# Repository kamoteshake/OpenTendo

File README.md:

<br />

# Open 'Tendo
An Open-Source HardWare (OSHW) recreation of the original 1985 Front-Loading NES motherboard.

## Note on RGB and HDMI

Neither RGB nor HDMI video output were or are a goal of the OpenTendo project, the goal was/is documentation and preservation, and the project was an exercise in reverse engineering. As such "improved" video outputs will not be added to OpenTendo.

NESRGB and Hi-Def NES can be installed as normal, but will not be incorporated into the OpenTendo PCB

## Repository Structure
### Branches
| Branch | Description |
| ------ | ----------- |
| master | Latest revision of OpenTendo. This is a almost 1:1 of the OEM NES. |
| modded | Modded version of the latest revision (`master`). This houses any modification that is not in the OEM NES. |
| vX.X | Previous revisions of OpenTendo. (*ex.* v1.3) |
| vX.X_modded | Modded version of a previous revision. (*ex.* v1.3_modded) |

### File Structure
```
.
├── BOM              # Contains the bill of materials.
├── Board Files      # Contains all files necessary to open the project in KiCad.
|   └── Libraries    # Contains a library of all of the custom footprints used on the board.
├── Scans            # Contains the scans of the OEM NES board.
└── Schematics       # Contains schematics for the OEM frontloading NES board revisions,
                       some schematics represent more than one revision
```

The gerber files required to order PCBs can be found under [releases](https://github.com/Redherring32/OpenTendo/releases).

## Recommended PCB specs
* 2 layers

* 119mmx196mm

* 1.6mm thickness

* HASL or ENiG surface finish

* And any color you want!

> [!IMPORTANT]
> OpenTendo have some solder mask overlapping the edge connector to secure the pads and the thin traces. Some fabricators might see this as an error and might try to fix it.
>
> We recommend leaving a note saying that the solder mask overlap on the edge connector is intentional and NOT an error when ordering the PCB.

The design is as true to the original board as possible, with subtle changes where needed to compensate for outdated/unsourcable parts,
as well as some improvements. (Expansion audio enabled, and other minor changes)

Since this project is open-source you may do as you like with it, whether that is to make boards for personal use, sell replacement NES boards, or to use the provided info for further custom PCB work/designs.

I am not in any way affiliated with Nintendo, I'm just doing this in my free time as a stepping stone into further Reverse Engineering work.

>[!NOTE]
> Please check the [BOM](./BOM#from-the-oem-nes) for the list of components needed from the OEM NES

## License

Licensed under
the TAPR Open Hardware License (www.tapr.org/OHL)

©Redherring32 2019-2024

## Credits
*=Lockster=* - Helping me tremendously along the way, keeping me from going insane, and cleaning up/helping with the final schematic. 

*Krzysiobal* - Putting together the NES-CPU-11 schematic that my schematic is largely referrenced against.

*[Muramasa](https://www.muramasaentertainment.com/)* - Ported to KiCad v8, PCB clean up, and fixing the EXP port footprint.

*[Kamoteshake](https://github.com/kamoteshake)* - Schematic clean up and fixing the EXP port footprint.

And to all of the awesome people in the NES scene, I wouldn't have been able to do this without the awesome work that some very clever people did before I got here.

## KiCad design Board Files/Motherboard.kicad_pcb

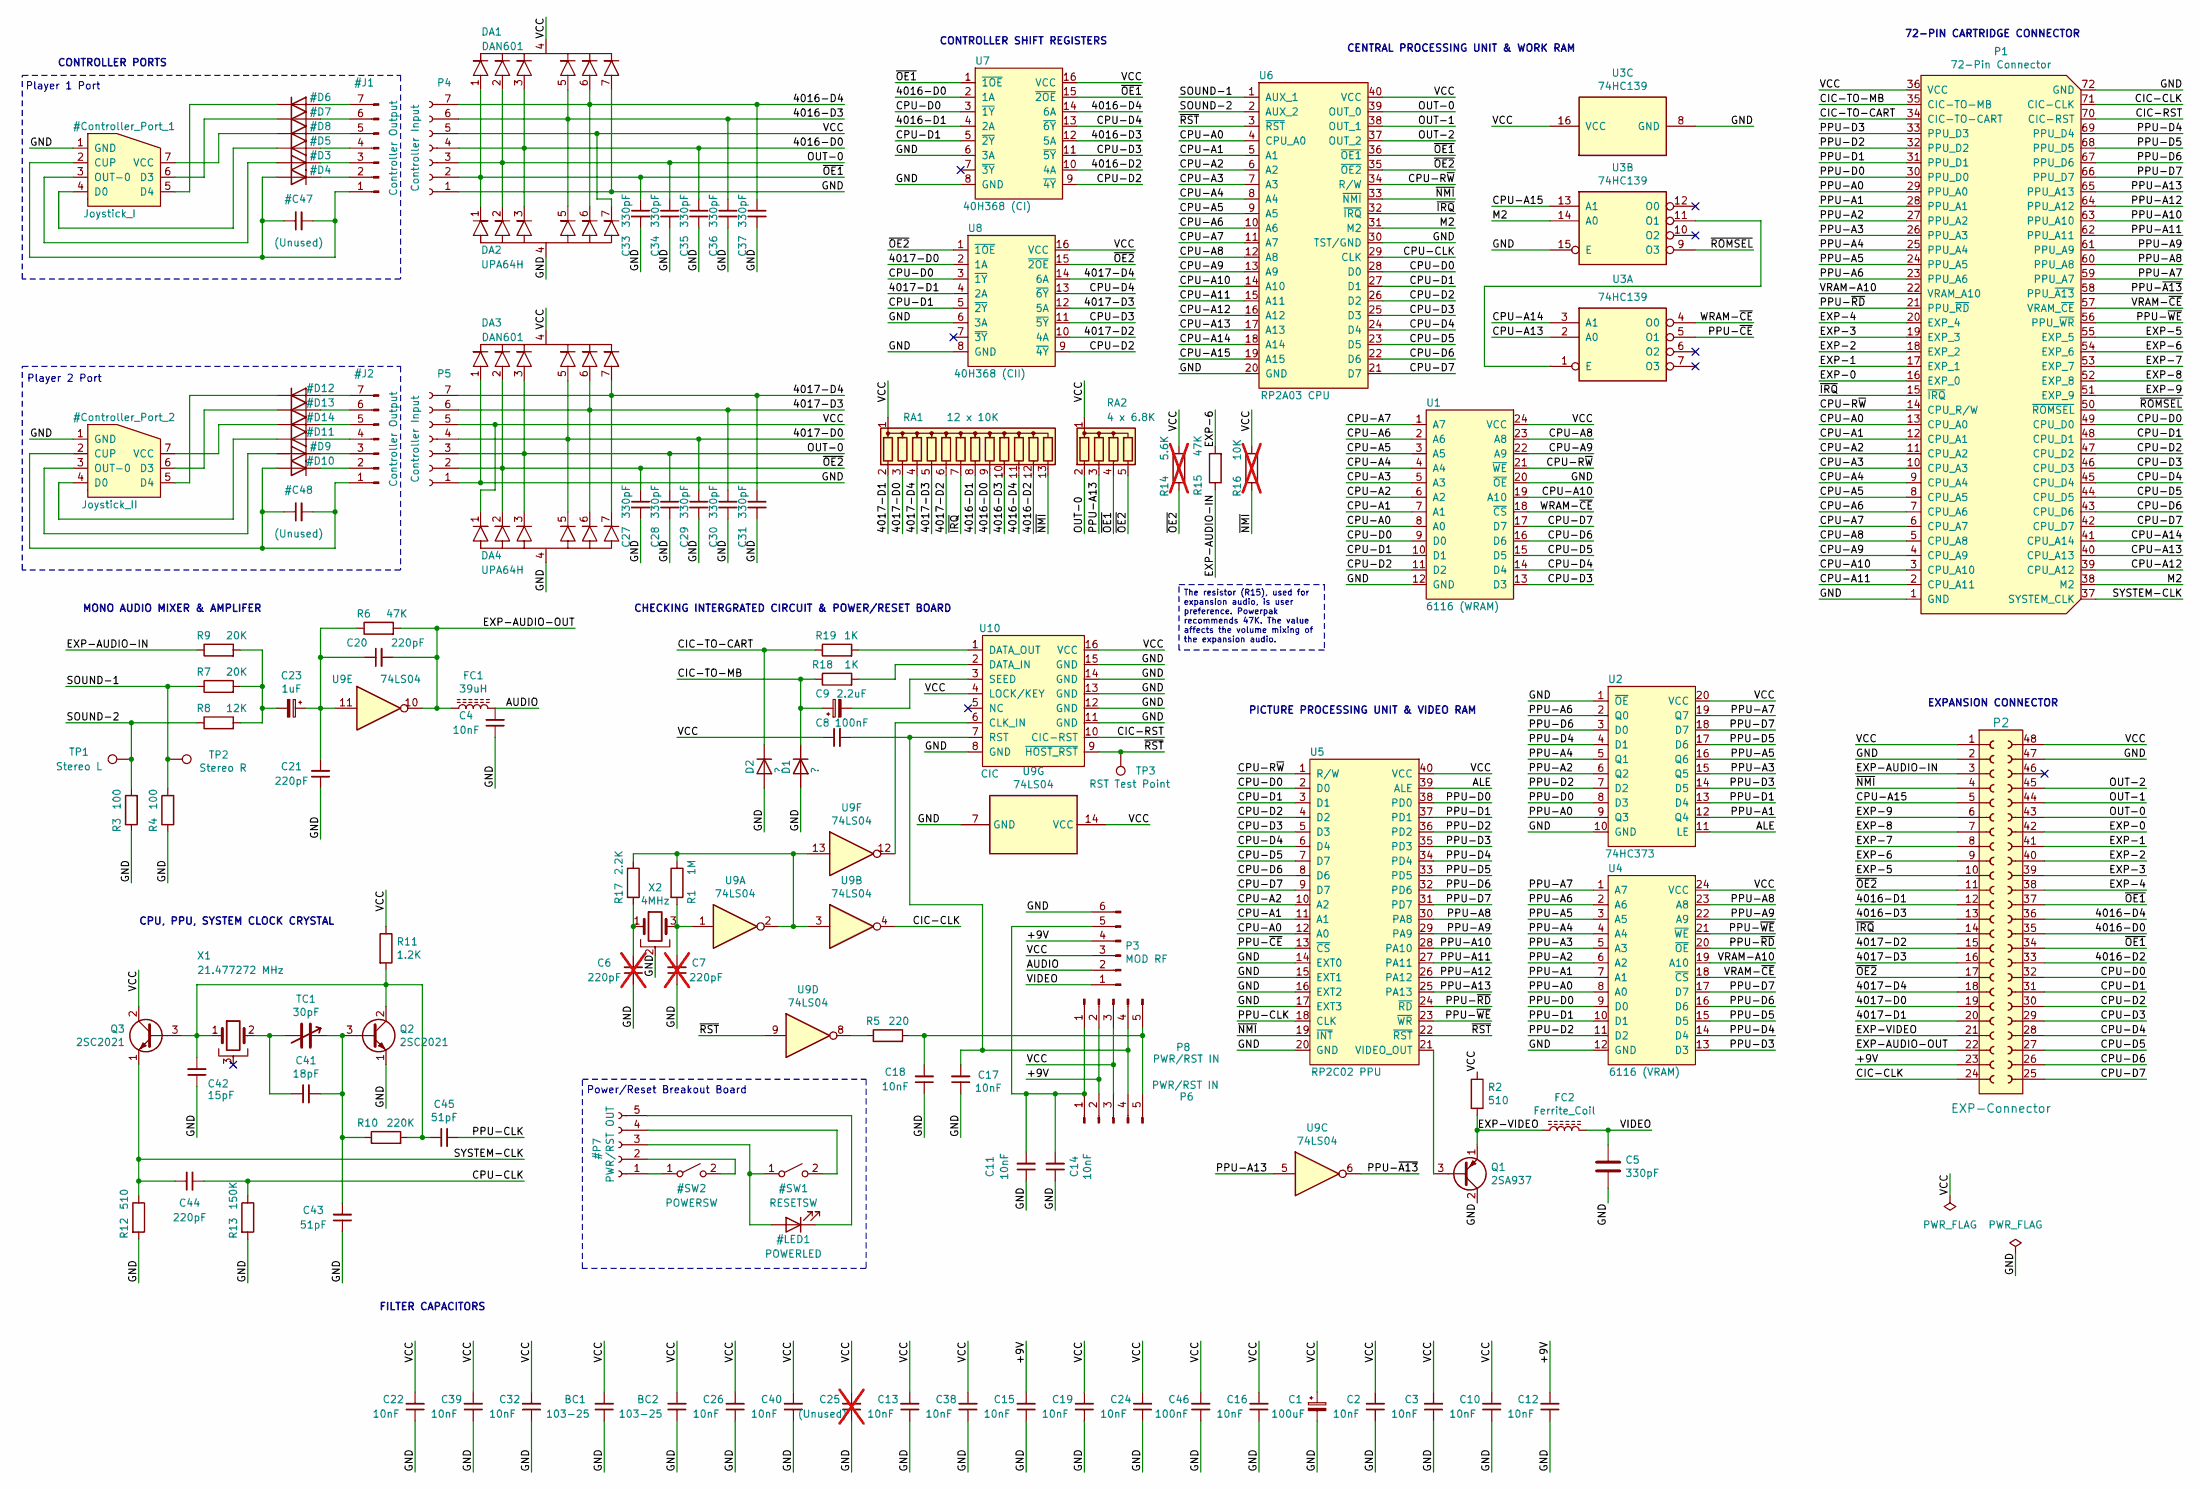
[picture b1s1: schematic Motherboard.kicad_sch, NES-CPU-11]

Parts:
BC1, BC2: 103-25; C_Disc_D6.0mm_W2.5mm_P5.00mm
C1: 100uF; CP_Radial_D5.0mm_P2.50mm
C2, C3, C4, C10, C11, C12, C13, C14, C15, C16, C17, C18, C19, C22, C24, C26, C32, C38, C39, C40: 10nF; C_Disc_D5.0mm_W2.5mm_P5.00mm
C5: 330pF; C_Disc_D3.0mm_W2.0mm_P2.50mm
C6, C7: 220pF; C_Disc_D3.0mm_W1.6mm_P2.50mm; not fitted
C8, C46: 100nF; C_Disc_D7.0mm_W2.5mm_P5.00mm
C9: 2.2uF; CP_Radial_D5.0mm_P2.50mm
C20, C21, C44: 220pF; C_Disc_D3.0mm_W1.6mm_P2.50mm
C23: 1uF; CP_Radial_D5.0mm_P2.50mm
C25: (Unused); C_Disc_D5.0mm_W2.5mm_P5.00mm; not fitted
C27, C28, C29, C30, C31, C33, C34, C35, C36, C37: 330pF; C_Disc_D3.0mm_W1.6mm_P2.50mm
C41: 18pF; C_Disc_D3.0mm_W2.0mm_P2.50mm
C42: 15pF; C_Disc_D3.4mm_W2.1mm_P2.50mm
C43, C45: 51pF; C_Disc_D3.4mm_W2.1mm_P2.50mm
D1, D2: ?; D_DO-35_SOD27_P10.16mm_Horizontal
DA1, DA3: DAN601; R_Array_SIP7
DA2, DA4: UPA64H; R_Array_SIP7
FC1: 39uH; R_Axial_DIN0207_L6.3mm_D2.5mm_P10.16mm_Horizontal
FC2: Ferrite_Coil; R_Axial_DIN0207_L6.3mm_D2.5mm_P10.16mm_Horizontal
P1: 72-Pin Connector; NES_Edge_Connector
P2: EXP-Connector; EXP_Header
P3: MOD RF; Mod_RF
P4, P5: Controller Input; JST_PH_S7B-PH-K_1x07_P2.00mm_Horizontal
P6: PWR/RST IN; PowerReset-switch-In
P8: PWR/RST IN; JST_PH_S5B-PH-K_1x05_P2.00mm_Horizontal
Q1: 2SA937; TO-126-3_Vertical_Short
Q2, Q3: 2SC2021; TO-126-3_Vertical_Short
R1: 1M; R_Axial_DIN0207_L6.3mm_D2.5mm_P10.16mm_Horizontal
R2, R12: 510; R_Axial_DIN0207_L6.3mm_D2.5mm_P10.16mm_Horizontal
R3, R4: 100; R_Axial_DIN0207_L6.3mm_D2.5mm_P10.16mm_Horizontal
R5: 220; R_Axial_DIN0207_L6.3mm_D2.5mm_P10.16mm_Horizontal
R6, R15: 47K; R_Axial_DIN0207_L6.3mm_D2.5mm_P10.16mm_Horizontal
R7, R9: 20K; R_Axial_DIN0207_L6.3mm_D2.5mm_P10.16mm_Horizontal
R8: 12K; R_Axial_DIN0207_L6.3mm_D2.5mm_P10.16mm_Horizontal
R10: 220K; R_Axial_DIN0207_L6.3mm_D2.5mm_P10.16mm_Horizontal
R11: 1.2K; R_Axial_DIN0207_L6.3mm_D2.5mm_P10.16mm_Horizontal
R13: 150K; R_Axial_DIN0207_L6.3mm_D2.5mm_P10.16mm_Horizontal
R14: 5.6K; R_Axial_DIN0207_L6.3mm_D2.5mm_P10.16mm_Horizontal; not fitted
R16: 10K; R_Axial_DIN0207_L6.3mm_D2.5mm_P10.16mm_Horizontal; not fitted
R17: 2.2K; R_Axial_DIN0207_L6.3mm_D2.5mm_P10.16mm_Horizontal
R18, R19: 1K; R_Axial_DIN0207_L6.3mm_D2.5mm_P10.16mm_Horizontal
RA1: 12 x 10K; R_Array_SIP13
RA2: 4 x 6.8K; R_Array_SIP5
TC1: 30pF; Trimmer_Cap_THT_5_5
TP1: Stereo L; TestPoint_Pad_1.5x1.5mm
TP2: Stereo R; TestPoint_Pad_1.5x1.5mm
TP3: RST Test Point; TestPoint_Pad_1.5x1.5mm
U1: 6116 (WRAM); DIP-24_W15.24-7.62mm_SOIC-24-15.4-7.6mm
U2: 74HC373; DIP-20_W7.62mm
U3: 74HC139; DIP-16_W7.62mm
U4: 6116 (VRAM); DIP-24_W15.24-7.62mm_SOIC-24-15.4-7.6mm
U5: RP2C02 PPU; DIP-40_W15.24mm
U6: RP2A03 CPU; DIP-40_W15.24mm
U7: 40H368 (CI); DIP-16_W7.62mm
U8: 40H368 (CII); DIP-16_W7.62mm
U9: 74LS04; DIP-14_W7.62mm
U10: CIC; DIP-16_W7.62mm
X1: 21.477272 MHz; Crystal_HC49-U_Horizontal_1EP_style2
X2: 4MHz; Resonator_Murata_CSTLSxxxG-3Pin_W8.0mm_H3.0mm

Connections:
/4016-D0: C35.1, DA1.3, DA2.3, P2.35, P4.4, RA1.9 (R8), U7.2 (1A)
/4016-D1: P2.12, RA1.8 (R7), U7.4 (2A)
/4016-D2: P2.33, RA1.12 (R11), U7.10 (4A)
/4016-D3: C36.1, DA1.5, DA2.5, P2.13, P4.6, RA1.10 (R9), U7.12 (5A)
/4016-D4: C37.1, DA1.6, DA2.6, P2.36, P4.7, RA1.11 (R10), U7.14 (6A)
/4017-D0: C29.1, DA3.5, DA4.5, P2.19, P5.4, RA1.3 (R2), U8.2 (1A)
/4017-D1: P2.20, RA1.2 (R1), U8.4 (2A)
/4017-D2: P2.15, RA1.6 (R5), U8.10 (4A)
/4017-D3: C30.1, DA3.6, DA4.6, P2.16, P5.6, RA1.5 (R4), U8.12 (5A)
/4017-D4: C31.1, DA3.7, DA4.7, P2.18, P5.7, RA1.4 (R3), U8.14 (6A)
/+9V: C12.2, C15.2, P2.23, P3.4, P6.2, P8.2
/ALE: U2.11 (LE), U5.39 (ALE)
/AUDIO: C4.2, FC1.2, P3.2
/CIC-CLK: P1.71 (CIC-CLK), P2.24, U9.4
/CIC-RST: P1.70 (CIC-RST), U10.10 (CIC-RST)
/CIC-TO-CART: D2.1 (K), P1.34 (CIC-TO-CART), R19.1
/CIC-TO-MB: C9.1, D1.1 (K), P1.35 (CIC-TO-MB), R18.1
/CPU-A0: P1.13 (CPU_A0), U1.8 (A0), U5.12 (A0), U6.4 (CPU_A0)
/CPU-A1: P1.12 (CPU_A1), U1.7 (A1), U5.11 (A1), U6.5 (A1)
/CPU-A2: P1.11 (CPU_A2), U1.6 (A2), U5.10 (A2), U6.6 (A2)
/CPU-A3: P1.10 (CPU_A3), U1.5 (A3~), U6.7 (A3)
/CPU-A4: P1.9 (CPU_A4), U1.4 (A4~), U6.8 (A4)
/CPU-A5: P1.8 (CPU_A5), U1.3 (A5~), U6.9 (A5)
/CPU-A6: P1.7 (CPU_A6), U1.2 (A6~), U6.10 (A6)
/CPU-A7: P1.6 (CPU_A7), U1.1 (A7), U6.11 (A7)
/CPU-A8: P1.5 (CPU_A8), U1.23 (A8), U6.12 (A8)
/CPU-A9: P1.4 (CPU_A9), U1.22 (A9), U6.13 (A9)
/CPU-A10: P1.3 (CPU_A10), U1.19 (A10), U6.14 (A10)
/CPU-A11: P1.2 (CPU_A11), U6.15 (A11)
/CPU-A12: P1.39 (CPU_A12), U6.16 (A12)
/CPU-A13: P1.40 (CPU_A13), U3.2 (A0), U6.17 (A13)
/CPU-A14: P1.41 (CPU_A14), U3.3 (A1), U6.18 (A14)
/CPU-A15: P2.5, U3.13 (A1), U6.19 (A15)
/CPU-CLK: C44.2, R13.1, U6.29 (CLK)
/CPU-D0: P1.49 (CPU_D0), P2.32, U1.9 (D0), U5.2 (D0), U6.28 (D0), U7.3 (~1Y), U8.3 (~1Y)
/CPU-D1: P1.48 (CPU_D1), P2.31, U1.10 (D1), U5.3 (D1), U6.27 (D1), U7.5 (~2Y), U8.5 (~2Y)
/CPU-D2: P1.47 (CPU_D2), P2.30, U1.11 (D2), U5.4 (D2), U6.26 (D2), U7.9 (~4Y), U8.9 (~4Y)
/CPU-D3: P1.46 (CPU_D3), P2.29, U1.13 (D3), U5.5 (D3), U6.25 (D3), U7.11 (~5Y), U8.11 (~5Y)
/CPU-D4: P1.45 (CPU_D4), P2.28, U1.14 (D4), U5.6 (D4), U6.24 (D4), U7.13 (~6Y), U8.13 (~6Y)
/CPU-D5: P1.44 (CPU_D5), P2.27, U1.15 (D5), U5.7 (D7), U6.23 (D5)
/CPU-D6: P1.43 (CPU_D6), P2.26, U1.16 (D6), U5.8 (D6), U6.22 (D6)
/CPU-D7: P1.42 (CPU_D7), P2.25, U1.17 (D7), U5.9 (D7), U6.21 (D7)
/CPU-R~W: P1.14 (CPU_R/W), U1.21 (~WE), U5.1 (R/W), U6.34 (R/W)
/EXP-0: P1.16 (EXP_0), P2.42
/EXP-1: P1.17 (EXP_1), P2.41
/EXP-2: P1.18 (EXP_2), P2.40
/EXP-3: P1.19 (EXP_3), P2.39
/EXP-4: P1.20 (EXP_4), P2.38
/EXP-5: P1.55 (EXP_5), P2.10
/EXP-6: P1.54 (EXP_6), P2.9, R15.2
/EXP-7: P1.53 (EXP_7), P2.8
/EXP-8: P1.52 (EXP_8), P2.7
/EXP-9: P1.51 (EXP_9), P2.6
/EXP-AUDIO-IN: P2.3, R9.1, R15.1
/EXP-AUDIO-OUT: C20.2, FC1.1, P2.22, R6.2, U9.10
/EXP-VIDEO: FC2.1, P2.21, Q1.1 (E), R2.2
/GND: BC1.1, BC2.1, C1.2, C2.1, C3.1, C4.1, C5.2, C6.1, C7.1, C10.1, C11.1, C12.1, C13.1, C14.1, C15.1, C16.1, C17.1, C18.1, C19.1, C21.1, C22.1, C24.1, C25.1, C26.1, C27.2, C28.2, C29.2, C30.2, C31.2, C32.1, C33.2, C34.2, C35.2, C36.2, C37.2, C38.1, C39.1, C40.1, C42.1, C43.1, C46.1, D1.2 (A), D2.2 (A), DA1.7, DA2.4, DA3.1, DA4.4, P1.1 (GND), P1.72 (GND), P2.2, P2.47, P3.6, P4.1, P5.1, Q1.2 (C), Q2.1 (E), R3.1, R4.1, R12.2, R13.2, U1.12 (GND~), U1.20 (~OE), U2.1 (~OE), U2.10 (GND), U3.8 (GND), U3.15 (E), U4.12 (GND~), U5.14 (EXT0), U5.15 (EXT1), U5.16 (EXT2), U5.17 (EXT3), U5.20 (GND), U6.20 (GND), U6.30 (TST/GND), U7.6 (3A), U7.8 (GND), U8.6 (3A), U8.8 (GND), U9.7 (GND), U10.8 (GND), U10.11 (GND), U10.12 (GND), U10.13 (GND), U10.14 (GND), U10.15 (GND), X2.2
/M2: P1.38 (M2), U3.14 (A0), U6.31 (M2)
/OUT-0: C28.1, C34.1, DA1.2, DA2.2, DA3.3, DA4.3, P2.43, P4.3, P5.3, RA2.2 (R1), U6.39 (OUT_0)
/OUT-1: P2.44, U6.38 (OUT_1)
/OUT-2: P2.45, U6.37 (OUT_2)
/PPU-A0: P1.29 (PPU_A0), U2.9 (Q3), U4.8 (A0)
/PPU-A1: P1.28 (PPU_A1), U2.12 (Q4), U4.7 (A1)
/PPU-A2: P1.27 (PPU_A2), U2.6 (Q2), U4.6 (A2)
/PPU-A3: P1.26 (PPU_A3), U2.15 (Q5), U4.5 (A3~)
/PPU-A4: P1.25 (PPU_A4), U2.5 (Q1), U4.4 (A4~)
/PPU-A5: P1.24 (PPU_A5), U2.16 (Q6), U4.3 (A5~)
/PPU-A6: P1.23 (PPU_A6), U2.2 (Q0), U4.2 (A6~)
/PPU-A7: P1.59 (PPU_A7), U2.19 (Q7), U4.1 (A7)
/PPU-A8: P1.60 (PPU_A8), U4.23 (A8), U5.30 (PA8)
/PPU-A9: P1.61 (PPU_A9), U4.22 (A9), U5.29 (PA9)
/PPU-A10: P1.63 (PPU_A10), U5.28 (PA10)
/PPU-A11: P1.62 (PPU_A11), U5.27 (PA11)
/PPU-A12: P1.64 (PPU_A12), U5.26 (PA12)
/PPU-A13: P1.65 (PPU_A13), RA2.3 (R2), U5.25 (PA13), U9.5
/PPU-CLK: C45.2, U5.18 (CLK)
/PPU-D0: P1.30 (PPU_D0), U2.8 (D3), U4.9 (D0), U5.38 (PD0)
/PPU-D1: P1.31 (PPU_D1), U2.13 (D4), U4.10 (D1), U5.37 (PD1)
/PPU-D2: P1.32 (PPU_D2), U2.7 (D2), U4.11 (D2), U5.36 (PD2)
/PPU-D3: P1.33 (PPU_D3), U2.14 (D5), U4.13 (D3), U5.35 (PD3)
/PPU-D4: P1.69 (PPU_D4), U2.4 (D1), U4.14 (D4), U5.34 (PD4)
/PPU-D5: P1.68 (PPU_D5), U2.17 (D6), U4.15 (D5), U5.33 (PD5)
/PPU-D6: P1.67 (PPU_D6), U2.3 (D0), U4.16 (D6), U5.32 (PD6)
/PPU-D7: P1.66 (PPU_D7), U2.18 (D7), U4.17 (D7), U5.31 (PD7)
/PPU-~A13: P1.58 (PPU_~A13), U9.6
/PPU-~CE: U3.5 (O1), U5.13 (~CS)
/PPU-~RD: P1.21 (PPU_~RD), U4.20 (~OE), U5.24 (~RD)
/PPU-~WE: P1.56 (PPU_~WR), U4.21 (~WE), U5.23 (~WR)
/SOUND-1: R4.2, R7.1, TP2.1, U6.1 (AUX_1)
/SOUND-2: R3.2, R8.1, TP1.1, U6.2 (AUX_2)
/SYSTEM-CLK: C44.1, P1.37 (SYSTEM_CLK), Q3.1 (E), R12.1
/VCC: BC1.2, BC2.2, C1.1, C2.2, C3.2, C8.1, C10.2, C13.2, C16.2, C19.2, C22.2, C24.2, C25.2, C26.2, C32.2, C38.2, C39.2, C40.2, C46.2, DA1.4, DA2.7, DA3.4, DA4.1, P1.36 (VCC), P2.1, P2.48, P3.3, P4.5, P5.5, P6.3, P8.3, Q3.2 (C), R2.1, R11.1, R14.1, R16.1, RA1.1 (common), RA2.1 (common), U1.24 (VCC), U2.20 (VCC), U3.16 (VCC), U4.24 (VCC), U5.40 (VCC), U6.40 (VCC), U7.16 (VCC), U8.16 (VCC), U9.14 (VCC), U10.4 (LOCK/KEY), U10.16 (VCC)
/VIDEO: C5.1, FC2.2, P3.1
/VRAM-A10: P1.22 (VRAM_A10), U4.19 (A10)
/VRAM-~CE: P1.57 (VRAM_~CE), U4.18 (~CS)
/WRAM-~CE: U1.18 (~CS), U3.4 (O0)
/~IRQ: P1.15 (~IRQ), P2.14, RA1.7 (R6), U6.32 (~IRQ)
/~NMI: P2.4, R16.2, RA1.13 (R12), U5.19 (~INT), U6.33 (~NMI)
/~OE1: C33.1, DA1.1, DA2.1, P2.34, P2.37, P4.2, RA2.4 (R3), U6.36 (~OE1), U7.1 (~1OE), U7.15 (~2OE)
/~OE2: C27.1, DA3.2, DA4.2, P2.11, P2.17, P5.2, R14.2, RA2.5 (R4), U6.35 (~OE2), U8.1 (~1OE), U8.15 (~2OE)
/~ROMSEL: P1.50 (~ROMSEL), U3.9 (O3)
/~RST: TP3.1, U5.22 (~RST), U6.3 (~RST), U9.9, U10.9 (~HOST_RST)
unnamed: C6.2, R17.2, X2.1
unnamed: C7.2, R1.2, U9.1, X2.3
unnamed: C20.1, C21.2, C23.1, R6.1, U9.11
unnamed: C23.2, R7.2, R8.2, R9.2
unnamed: C41.1, TC1.2, X1.2
unnamed: C11.2, C14.2, P3.5, P6.1, P8.1
unnamed: C8.2, C17.2, P6.4, P8.4, U10.7 (RST)
unnamed: C18.2, P6.5, P8.5, R5.2
unnamed: Q1.3 (B), U5.21 (VIDEO_OUT)
unnamed: C41.2, C43.2, Q2.3 (B), R10.1, TC1.1
unnamed: C42.2, C45.1, Q2.2 (C), Q3.3 (B), R10.2, R11.2, X1.1
unnamed: R1.1, R17.1, U9.2, U9.3, U9.13
unnamed: R5.1, U9.8
unnamed: U3.1 (E), U3.11 (O1)
unnamed: U9.12, U10.6 (CLK_IN)
unnamed: R18.2, U10.2 (DATA_IN)
unnamed: R19.2, U10.1 (DATA_OUT)
unnamed: C9.2, U10.3 (SEED)

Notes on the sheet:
72-PIN CARTRIDGE CONNECTOR
MONO AUDIO MIXER & AMPLIFER
CENTRAL PROCESSING UNIT & WORK RAM
CONTROLLER PORTS
EXPANSION CONNECTOR
FILTER CAPACITORS
Player 2 Port
Player 1 Port
Power/Reset Breakout Board
CHECKING INTERGRATED CIRCUIT & POWER/RESET BOARD
PICTURE PROCESSING UNIT & VIDEO RAM
CPU, PPU, SYSTEM CLOCK CRYSTAL
CONTROLLER SHIFT REGISTERS
The resistor (R15), used for expansion audio, is user preference. Powerpak recommends 47K. The value affects the volume mixing of the expansion audio.

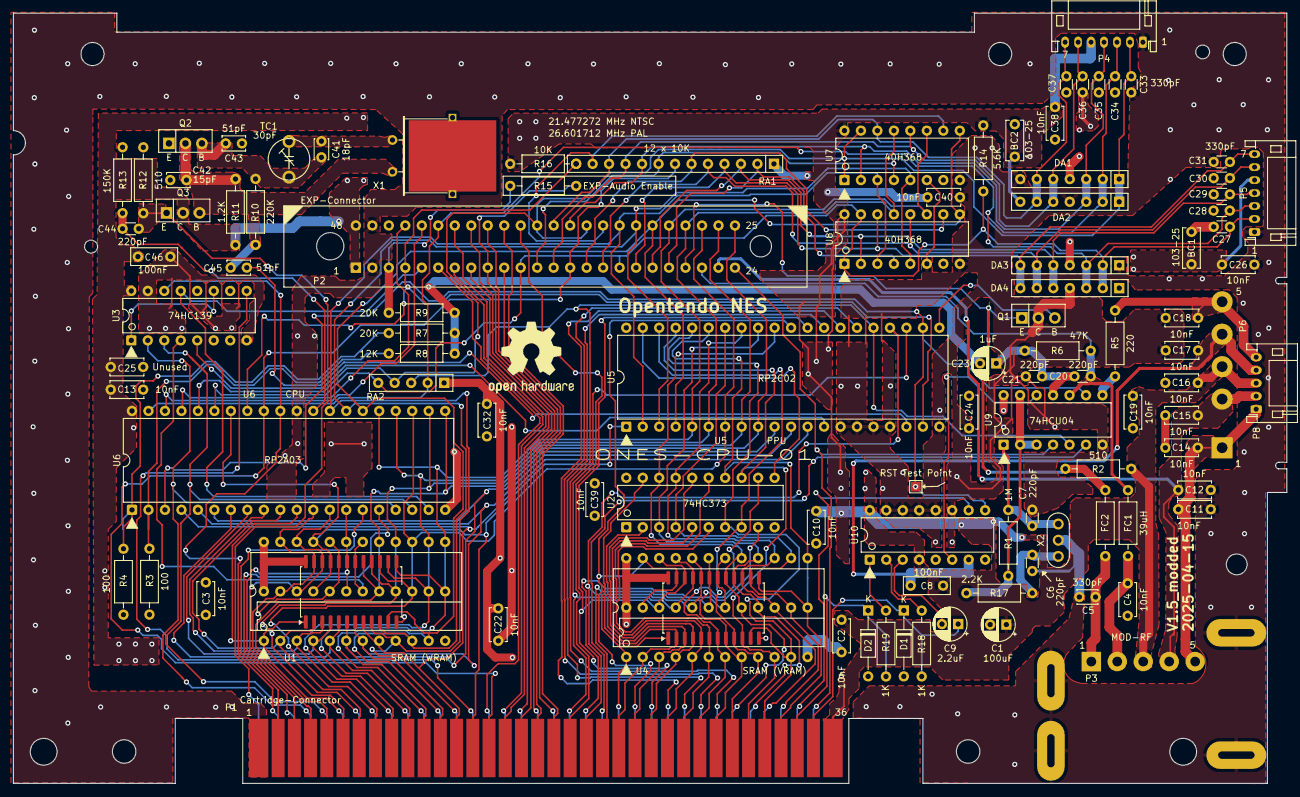
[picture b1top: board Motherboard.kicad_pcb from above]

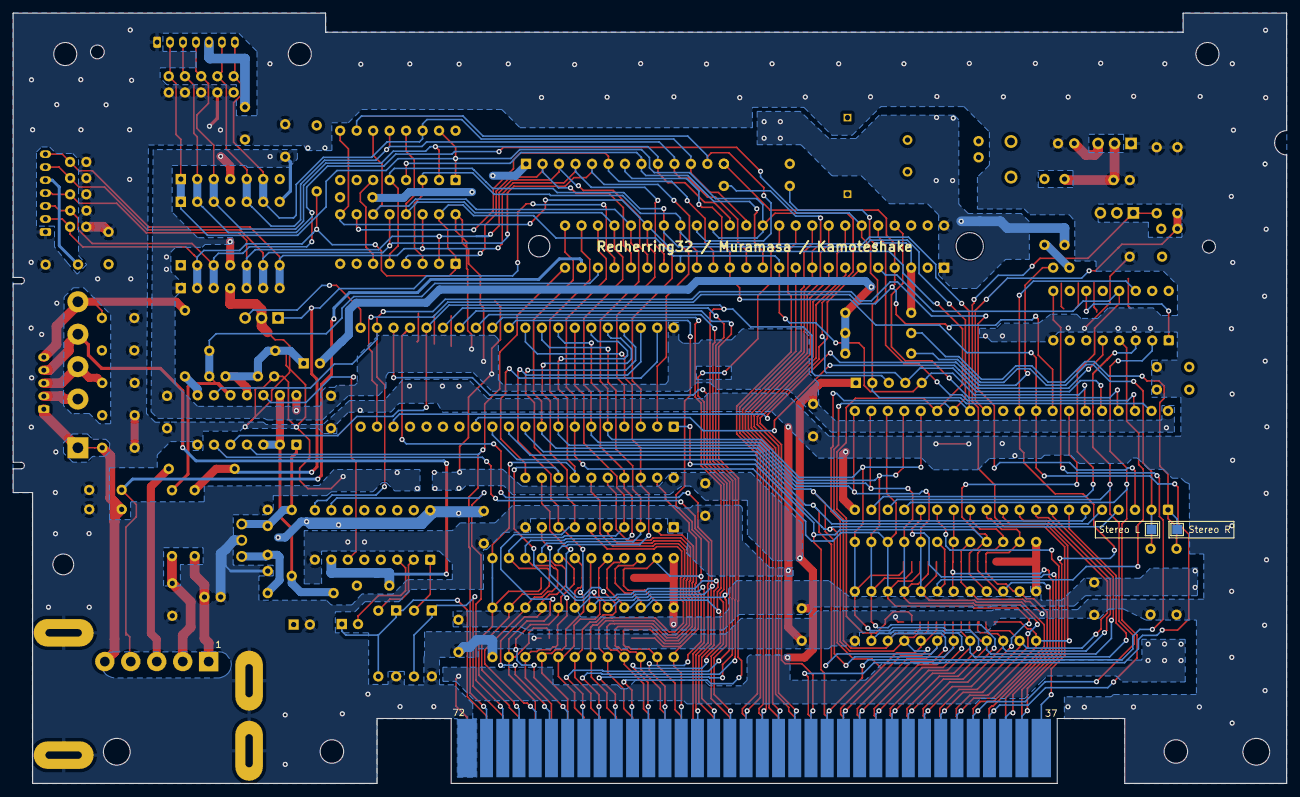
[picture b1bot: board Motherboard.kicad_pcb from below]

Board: 2 copper layers, 196.3 x 118.7 mm, 103 parts (2 on the bottom side), 120 nets.

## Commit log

2025-04-15 feat: port to kicad v9
2025-04-15 fix: diode array symbols
2025-04-15 feat: updated kicad v9 symbols
2025-04-15 fix: 74HC368 bus pin type
2025-04-15 feat: added power flag to gnd and vcc nets
2025-04-15 fix: changed ppu ext pins to passive
2025-04-15 feat: updated footprints to fix DRC errors and warnings
2025-04-15 chore: update versions
2025-04-15 chore: updated version and date on board
2025-04-15 feat: updated interactive bom
2025-04-15 chore: generated gerber
2025-04-15 feat: updated schematic pdf
2025-04-15 fix: schematic pdf
2025-04-15 Revert "fix: schematic pdf"
    This reverts commit c2a11825958983589db0d85ac6bd32a988f3aabb.
2025-04-15 Revert "feat: updated schematic pdf"
    This reverts commit 49c123eb4557a532feba8fa6d5b54b9a2afe2368.
2025-04-15 feat: added R1 and C40 value on silkscreen
2025-04-15 feat: updated trimmer cap footprint
2025-04-15 chore: updated date on board
